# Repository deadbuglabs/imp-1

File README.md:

# IMP-1 firmware

ESP32-S3 firmware for **IMP-1**, the Deadbug Labs portable hardware
exploration device. Twelve tools on a frozen C API (`include/imp_api.h`),
one common shell, partial-redraw UI on a 172x320 ST7789 display.

## Tools

Sub-GHz · NFC · IR · BadUSB · GPIO · U2F · Archive · Flash Lab ·
Security Auto-Audit (passive) — plus RFID / iButton / 1-Wire as guarded
stubs that land on IMP-2 hardware.

## Build status

Clean build (PlatformIO, ESP32-S3):

- **0 errors, 0 warnings**
- RAM 41.2% · Flash 43.9%
- Full detail: [BUILD_REPORT.md](BUILD_REPORT.md)

```sh
pio run
```

## Caveats

- **U2F host interop is unverified** — the CTAP1/ECDSA engine compiles and
  is structurally complete; it has not yet been tested against a live host.
  It is the #1 bring-up verification item.
- **The boards are not yet fabricated.** Main board v13 (wider
  respin): 17 unconnected nets remain, with 0 clearance violations
  and 0 shorts; the remaining 17 are accepted bodge wires, one frozen
  net, and fence-proven items measured in the routing log. The NFC
  board is DRC-clean and the IR board's routing is done. Gate 3
  (PCB integrity) has not passed yet. This firmware is ready to
  flash the day a main board exists.
- Sub-GHz capture is FIFO-derived (the current board revision does not
  connect CC1101 GDO0/GDO2); true edge capture is an IMP-2 item.

## Sponsors

**[PCBWay](https://www.pcbway.com)** — 3D-printing sponsor: a USD 30
3D-print credit (no expiry; splits across two orders), held until the
boards are fabricated and fit-checked, then it prints the cases.

Project site: [deadbuglabs.github.io](https://deadbuglabs.github.io)

— Deadbug Labs

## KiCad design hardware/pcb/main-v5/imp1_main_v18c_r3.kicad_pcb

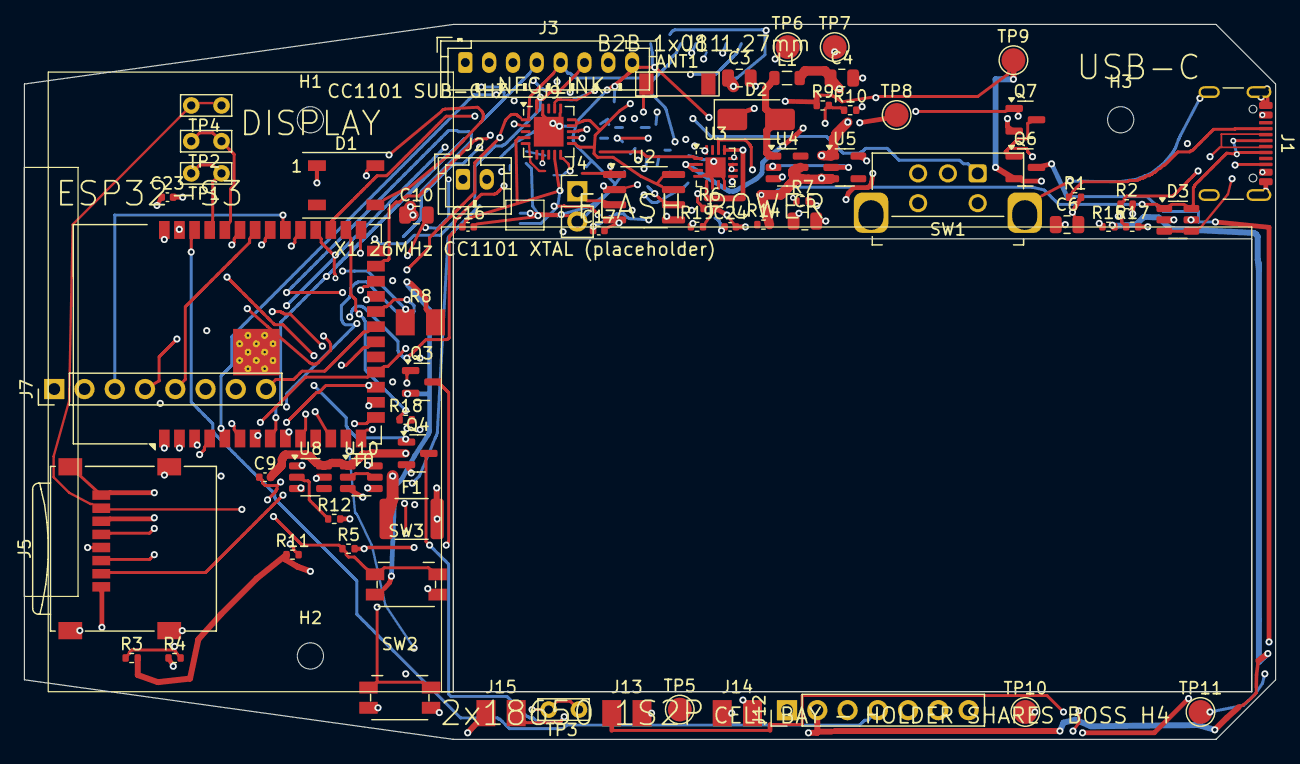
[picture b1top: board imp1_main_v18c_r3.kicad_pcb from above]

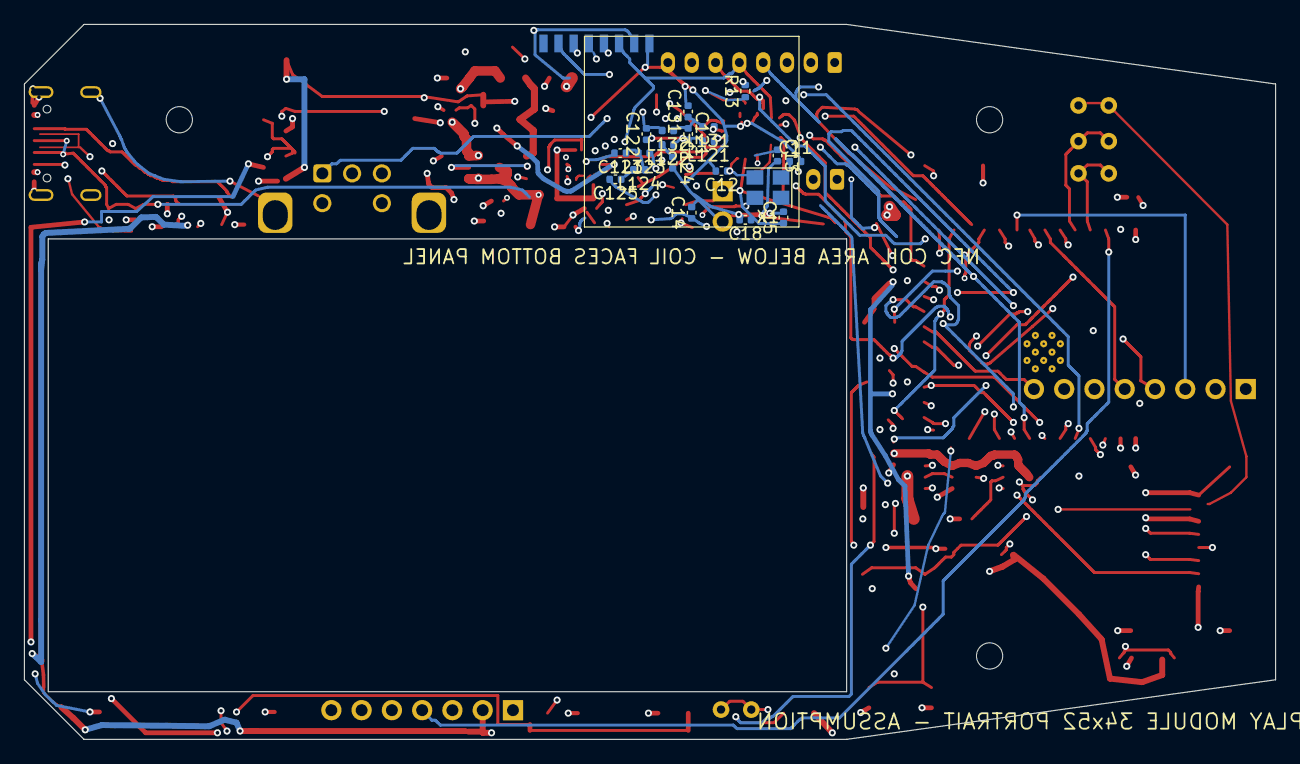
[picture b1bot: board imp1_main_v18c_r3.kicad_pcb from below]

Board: 4 copper layers, 105.0 x 60.0 mm, 93 parts (20 on the bottom side), 78 nets.

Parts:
ANT1: Johanson 0915AT43A0026E 915MHz chip ante; IMP1_Johanson_0915AT43A0026
C3, C6, C10: 10uF X5R; C_0805_2012Metric
C4, C5: 22uF X5R; C_0805_2012Metric
C9: 0.1uF; C_0402_1005Metric
C11, C12: 27pF NP0; C_0402_1005Metric
C13: 100nF X5R; C_0402_1005Metric
C14, C15, C16, C17, C18, C23, C24: 100nF; C_0402_1005Metric
C121: TI balun C121 1.0pF +-0.25 NP0; C_0402_1005Metric
C122: TI balun C122 1.5pF +-0.25 NP0; C_0402_1005Metric
C123: TI match C123 3.3pF +-0.25 NP0; C_0402_1005Metric
C124: TI balun C124 100pF +-5% NP0; C_0402_1005Metric
C125: TI C125 12pF +-5% NP0; C_0402_1005Metric
C131: TI balun C131 1.5pF +-0.25 NP0; C_0402_1005Metric
D1: WS2812B addressable LED; LED_WS2812B_PLCC4_5.0x5.0mm_P3.2mm
D2: SS34 3A Schottky; D_SMA
D3: USBLC6-2SC6 USB ESD array; SOT-23-6
F1: PTC resettable Ihold 3.0A Itrip 6.0A Vma; Fuse_1812_4532Metric
H1, H2, H3: M2_BOSS_EST; MountingHole_2.2mm_M2
J1: USB-C receptacle 16-pin mid-mount; USB_C_Receptacle_GCT_USB4105-xx-A_16P_TopMnt_Horizontal
J2: JST PH 2-pin battery connector; JST_PH_B2B-PH-K_1x02_P2.00mm_Vertical
J3: JST PH 8-pin B8B-PH-K-S class; JST_PH_B8B-PH-K_1x08_P2.00mm_Vertical
J4: 2-pin header = physical flash WP# lock; PinHeader_1x02_P2.54mm_Vertical
J5: microSD socket; microSD_HC_Wuerth_693072010801
J7: keypad matrix connector 8-pin; PinHeader_1x08_P2.54mm_Vertical
J11: B2B 1x08 1.27mm
J12: 1x07 2.54mm header; PinHeader_1x07_P2.54mm_Vertical
J13: 1x02 land pair A9 camera power; IMP1_LandPair_1x02
J14: 1x02 land pair buzzer; IMP1_LandPair_1x02
J15: 1x02 land pair flash LED; IMP1_LandPair_1x02
L1: 4.7uH Isat>=3A; L_0805_2012Metric
L121: TI balun L121 12nH +-5% Murata LQW15 wir; L_0402_1005Metric
L122: TI balun L122 18nH +-5%; L_0402_1005Metric
L123: TI match L123 12nH +-5% Murata LQW15; L_0402_1005Metric
L124: TI match L124 12nH +-5% Murata LQW15; L_0402_1005Metric
L131: TI balun L131 12nH +-5% Murata LQW15 wir; L_0402_1005Metric
L132: TI balun L132 18nH +-5% Murata LQW15; L_0402_1005Metric
Q3: MMBT3904 NPN low-side buzzer switch; SOT-23
Q4: AO3400A; SOT-23
Q6: AO3401A P-channel; SOT-23
Q7: 2N7002; SOT-23
R1, R2: 5.1k 1%; R_0402_1005Metric
R3: 300k 1%; R_0402_1005Metric
R4: 100k 1%; R_0402_1005Metric
R5, R14: 10k; R_0402_1005Metric
R6: 750R 1%; R_0402_1005Metric
R7: 1.2k 1%; R_0402_1005Metric
R8: 10K NTC B3435 leaded bead bonded to cell; IMP1_LandPair_1x02
R9: 75k 1%; R_0402_1005Metric
R10: 10k 1%; R_0402_1005Metric
R11: 100R; R_0402_1005Metric
R12, R18: 1k; R_0402_1005Metric
R13: 56k 1%; R_0402_1005Metric
R15, R17: 100k; R_0402_1005Metric
R19: 72k 1%; R_0402_1005Metric
SW1: EC11E rotary encoder with push; RotaryEncoder_PEC12R_H_MP
SW2: tactile switch; Panasonic_EVQPUJ_EVQPUA
SW3: panel key assigned RESET; Panasonic_EVQPUJ_EVQPUA
TP1: test pad UART_TX; TestPoint_Bridge_Pitch2.54mm_Drill0.7mm
TP2: test pad UART_RX; TestPoint_Bridge_Pitch2.54mm_Drill0.7mm
TP3: test pad SPI_SCLK; TestPoint_Bridge_Pitch2.54mm_Drill0.7mm
TP4: test pad SPI_MISO; TestPoint_Bridge_Pitch2.54mm_Drill0.7mm
TP5: test pad CHG_PGOOD; TestPoint_Pad_D2.0mm
TP6: test pad CHG_STAT; TestPoint_Pad_D2.0mm
TP7: test pad VBUS_5V; TestPoint_Pad_D2.0mm
TP8: test pad BAT_CELL; TestPoint_Pad_D2.0mm
TP9: test pad BOOST_5V; TestPoint_Pad_D2.0mm
TP10: test pad V3_3; TestPoint_Pad_D2.0mm
TP11: test pad GND; TestPoint_Pad_D2.0mm
U1: ESP32-S3-WROOM-1-N8R2; ESP32-S3-WROOM-1
U2: W25Q64JVSSIQ or MX25L6406E NOR flash SOL; SOIC-8_3.9x4.9mm_P1.27mm
U3: BQ24074RGTR charger/power-path; QFN-16-1EP_3x3mm_P0.5mm_EP1.7x1.7mm
U4: MT3608 boost; SOT-23-6
U5: AP2112K-3.3 LDO; SOT-23-5
U8: DW01A-G protection IC; SOT-23-6
U9: CC1101 RF transceiver; QFN-20-1EP_4x4mm_P0.5mm_EP2.5x2.5mm
U10: FS8205A dual N-FET SOT-23-6 VARIANT ONLY; SOT-23-6
X1: 26.000MHz crystal CL=16pF; Crystal_SMD_3225-4Pin_3.2x2.5mm

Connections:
A9_5V: J13.1, Q6.3
A9_GATE: Q6.1, Q7.3, R15.1
A9_PWR: Q7.1, R17.1, U1.12
BAL_A: C121.1, C131.1, L131.2, L132.1
BAL_B: C121.2, C122.1, L121.2, L122.1
BAL_BDC: C124.1, L122.2
BAL_C: C122.2, L123.1, L132.2
BAL_D: C123.1, L123.2, L124.1
BAL_E: C125.1, L124.2
BATT_ADC: R3.1, R4.2, U1.4
BAT_CELL: C10.1, F1.2, R3.2, R11.1, TP8.1, U3.2, U3.3
BOOST_5V: C5.1, D2.1, J12.2, J15.1, Q6.2, R9.1, R15.2, TP9.1
BOOST_FB: R9.2, R10.1, U4.3
BOOST_SW: D2.2, L1.1, U4.1
BOOT: SW2.1, U1.27
BUZZER: R18.1, U1.28
BZR_BASE: Q3.1, R18.2
BZR_OUT: J14.2, Q3.3
CC1: J1.A5, R1.1
CC2: J1.B5, R2.1
CC_CS: U1.11, U9.7
CC_DCOUPL: C13.1, U9.5
CC_RBIAS: R13.1, U9.17
CC_XOSC_Q1: C11.1, U9.8, X1.1
CC_XOSC_Q2: C12.1, U9.10, X1.2
CELL_NEG: C9.2, J2.2, U8.6, U10.1
CELL_POS: F1.1, J2.1
CHG_ILIM: R7.1, U3.12
CHG_ISET: R6.1, U3.16
CHG_PGOOD: R14.1, TP5.1, U3.7
CHG_STAT: TP6.1, U3.9
CHG_TMR: R19.1, U3.14
CHG_TS: R8.1, U3.1
COL1: J7.5, U1.34
COL2: J7.6, U1.35
COL3: J7.7, U1.22
COL4: J7.8, U1.21
DISP_BL: J3.7, U1.7
DISP_CS: J3.2, U1.10
DISP_DC: J3.3, U1.9
DISP_RST: J3.4, U1.8
EN: R5.1, SW3.1, U1.3
ENC_A: SW1.A, U1.5
ENC_B: SW1.B, U1.29
ENC_PUSH: SW1.S1, U1.30
FLASHLED_GATE: Q4.1, U1.39
FLASHLED_OUT: J15.2, Q4.3
FLASH_CS: U1.23, U2.1
FLASH_WP: J4.1, U2.3
GND: C3.2, C4.2, C5.2, C6.2, C10.2, C11.2, C12.2, C13.2, C14.2, C15.2, C16.2, C17.2, C18.2, C23.2, C24.2, C123.2, C124.2, C131.2, D1.3, D3.2, J1.A1, J1.A12, J1.B1, J1.B12, J1.S1, J3.8, J4.2, J5.1, J5.6, J5.8, J5.9, J11.1, J12.1, J12.7, J13.2, Q3.2, Q4.2, Q7.2, R1.2, R2.2, R4.1, R6.2, R7.2, R8.2, R10.2, R12.2, R13.2, R17.2, R19.2, SW1.C, SW1.MP, SW1.S2, SW2.2, SW3.2, TP11.1, U1.1, U1.40, U1.41, U2.4, U3.4, U3.6, U3.8, U3.17, U4.2, U5.2, U9.16, U9.19, U9.21, U10.3
IR_RX_OUT: J12.5, U1.16
IR_TX: J12.4, U1.38
LED_DATA: D1.4, U1.6
PROT_CS: R12.1, U8.2
PROT_DMID: U10.2, U10.5
PROT_OC: U8.3, U10.4
PROT_OD: U8.1, U10.6
PROT_VDD_F: C9.1, R11.2, U8.5
RF_ANT: ANT1.1, C125.2
RF_N: L131.1, U9.13
RF_P: L121.1, U9.12
ROW1: J7.1, U1.20
ROW2: J7.2, U1.31
ROW3: J7.3, U1.32
ROW4: J7.4, U1.33
SD_CS: J5.2, U1.15
SPI_MISO: J5.7, J11.5, TP4.1, U1.19, U2.2, U9.2
SPI_MOSI: J3.6, J5.3, J11.4, U1.17, U2.5, U9.20
SPI_SCLK: J3.5, J5.5, J11.3, TP3.1, U1.18, U2.6, U9.1
ST25_CS: J11.6, U1.24
ST25_IRQ: J11.7, U1.25
SYS_5V: C4.1, L1.2, R14.2, U3.10, U3.11, U4.4, U4.5, U5.1, U5.3
UART_RX: TP2.1, U1.36
UART_TX: TP1.1, U1.37
USB_DN: D3.3, D3.4, J1.A7, J1.B7, U1.13
USB_DP: D3.1, D3.6, J1.A6, J1.B6, U1.14
V3_3: C6.1, C14.1, C15.1, C16.1, C17.1, C18.1, C23.1, C24.1, D1.1, J3.1, J5.4, J11.2, J12.3, J14.1, R5.2, TP10.1, U1.2, U2.7, U2.8, U5.5, U9.4, U9.9, U9.11, U9.14, U9.15, U9.18
VBUS_5V: C3.1, D3.5, J1.A4, J1.A9, J1.B4, J1.B9, TP7.1, U3.5, U3.13
